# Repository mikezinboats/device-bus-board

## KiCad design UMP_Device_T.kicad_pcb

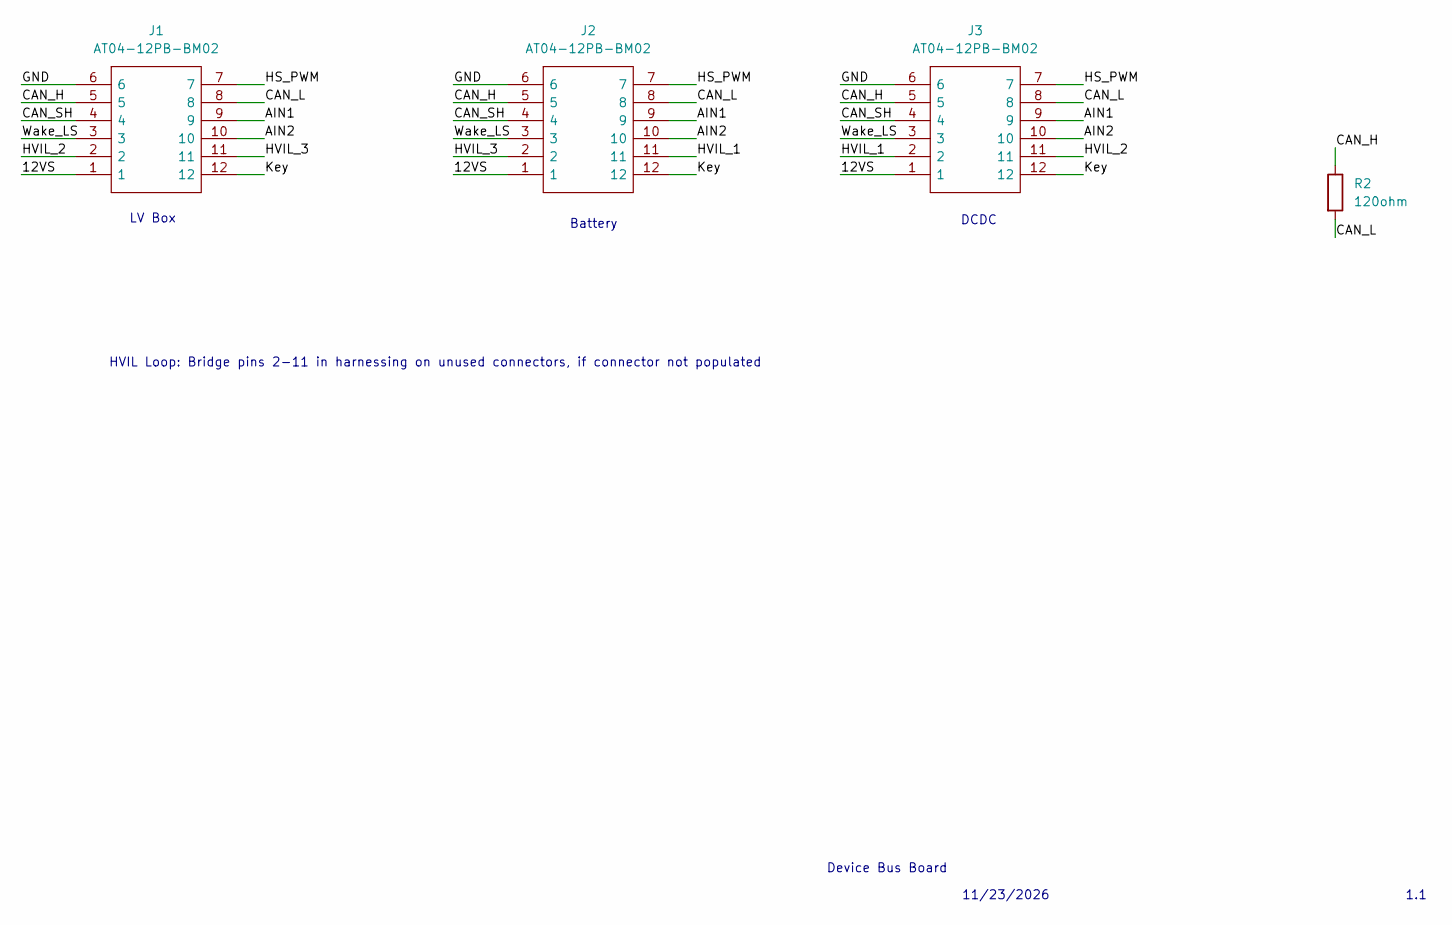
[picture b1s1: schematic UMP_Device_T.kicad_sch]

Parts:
J1, J2, J3: AT04-12PB-BM02; AT0412PBBM02; Mouser Part Number 654-AT04-12PB-BM02
R2: 120ohm; R_0603_1608Metric

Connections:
/12VS: J1.1, J2.1, J3.1
/AIN1: J1.9, J2.9, J3.9
/AIN2: J1.10, J2.10, J3.10
/CAN_H: J1.5, J2.5, J3.5, R2.1
/CAN_L: J1.8, J2.8, J3.8, R2.2
/CAN_SH: J1.4, J2.4, J3.4
/GND: J1.6, J2.6, J3.6
/HS_PWM: J1.7, J2.7, J3.7
/HVIL_1: J2.11, J3.2
/HVIL_2: J1.2, J3.11
/HVIL_3: J1.11, J2.2
/Key: J1.12, J2.12, J3.12
/Wake_LS: J1.3, J2.3, J3.3

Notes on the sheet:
Battery
1.1
LV Box
Device Bus Board
DCDC
HVIL Loop: Bridge pins 2-11 in harnessing on unused connectors, if connector not populated
11/23/2026

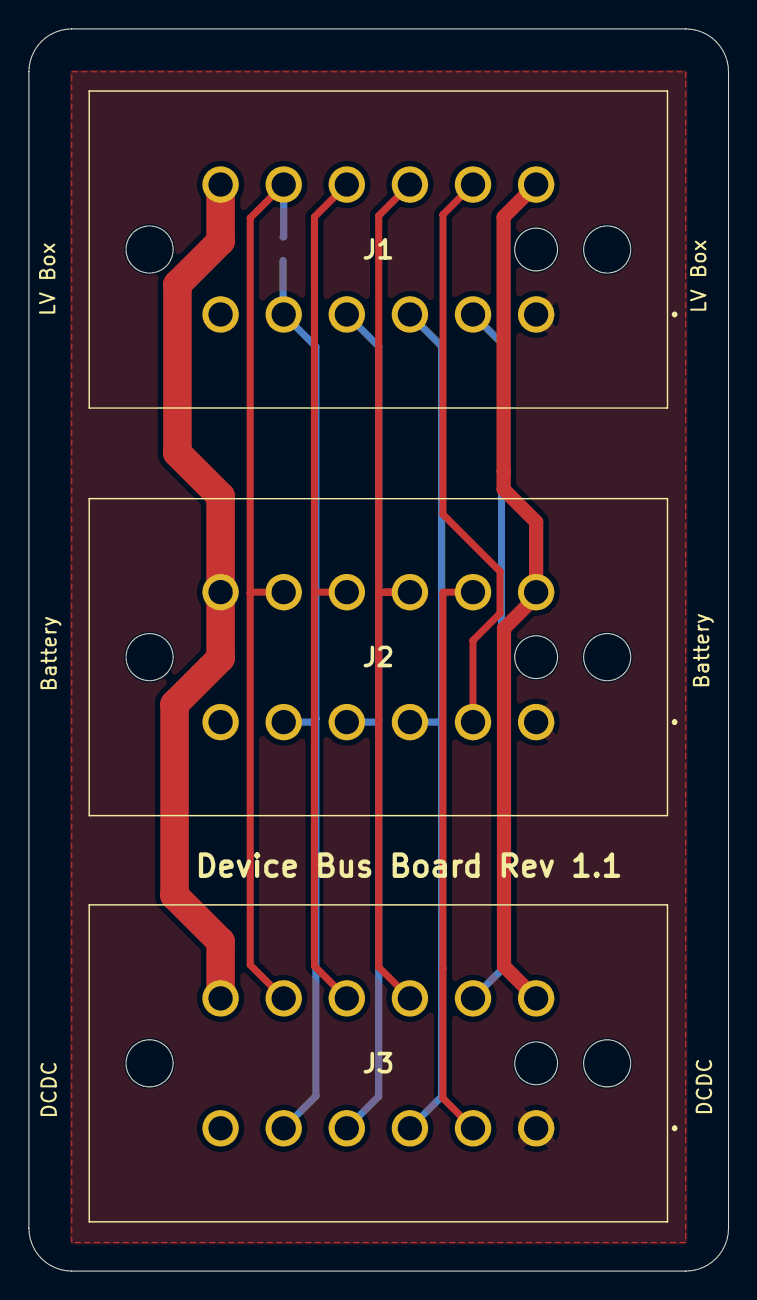
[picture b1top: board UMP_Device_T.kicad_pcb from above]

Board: 2 copper layers, 49.0 x 87.0 mm, 4 parts (1 on the bottom side), 13 nets.
